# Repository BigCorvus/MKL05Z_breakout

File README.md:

# MKL05Z_breakout
Breakout board for the MKL05Z32VFM4 Corte M0 microcontroller by Freescale. 
See http://www.thinkering.de/cms/?p=656 for more info.

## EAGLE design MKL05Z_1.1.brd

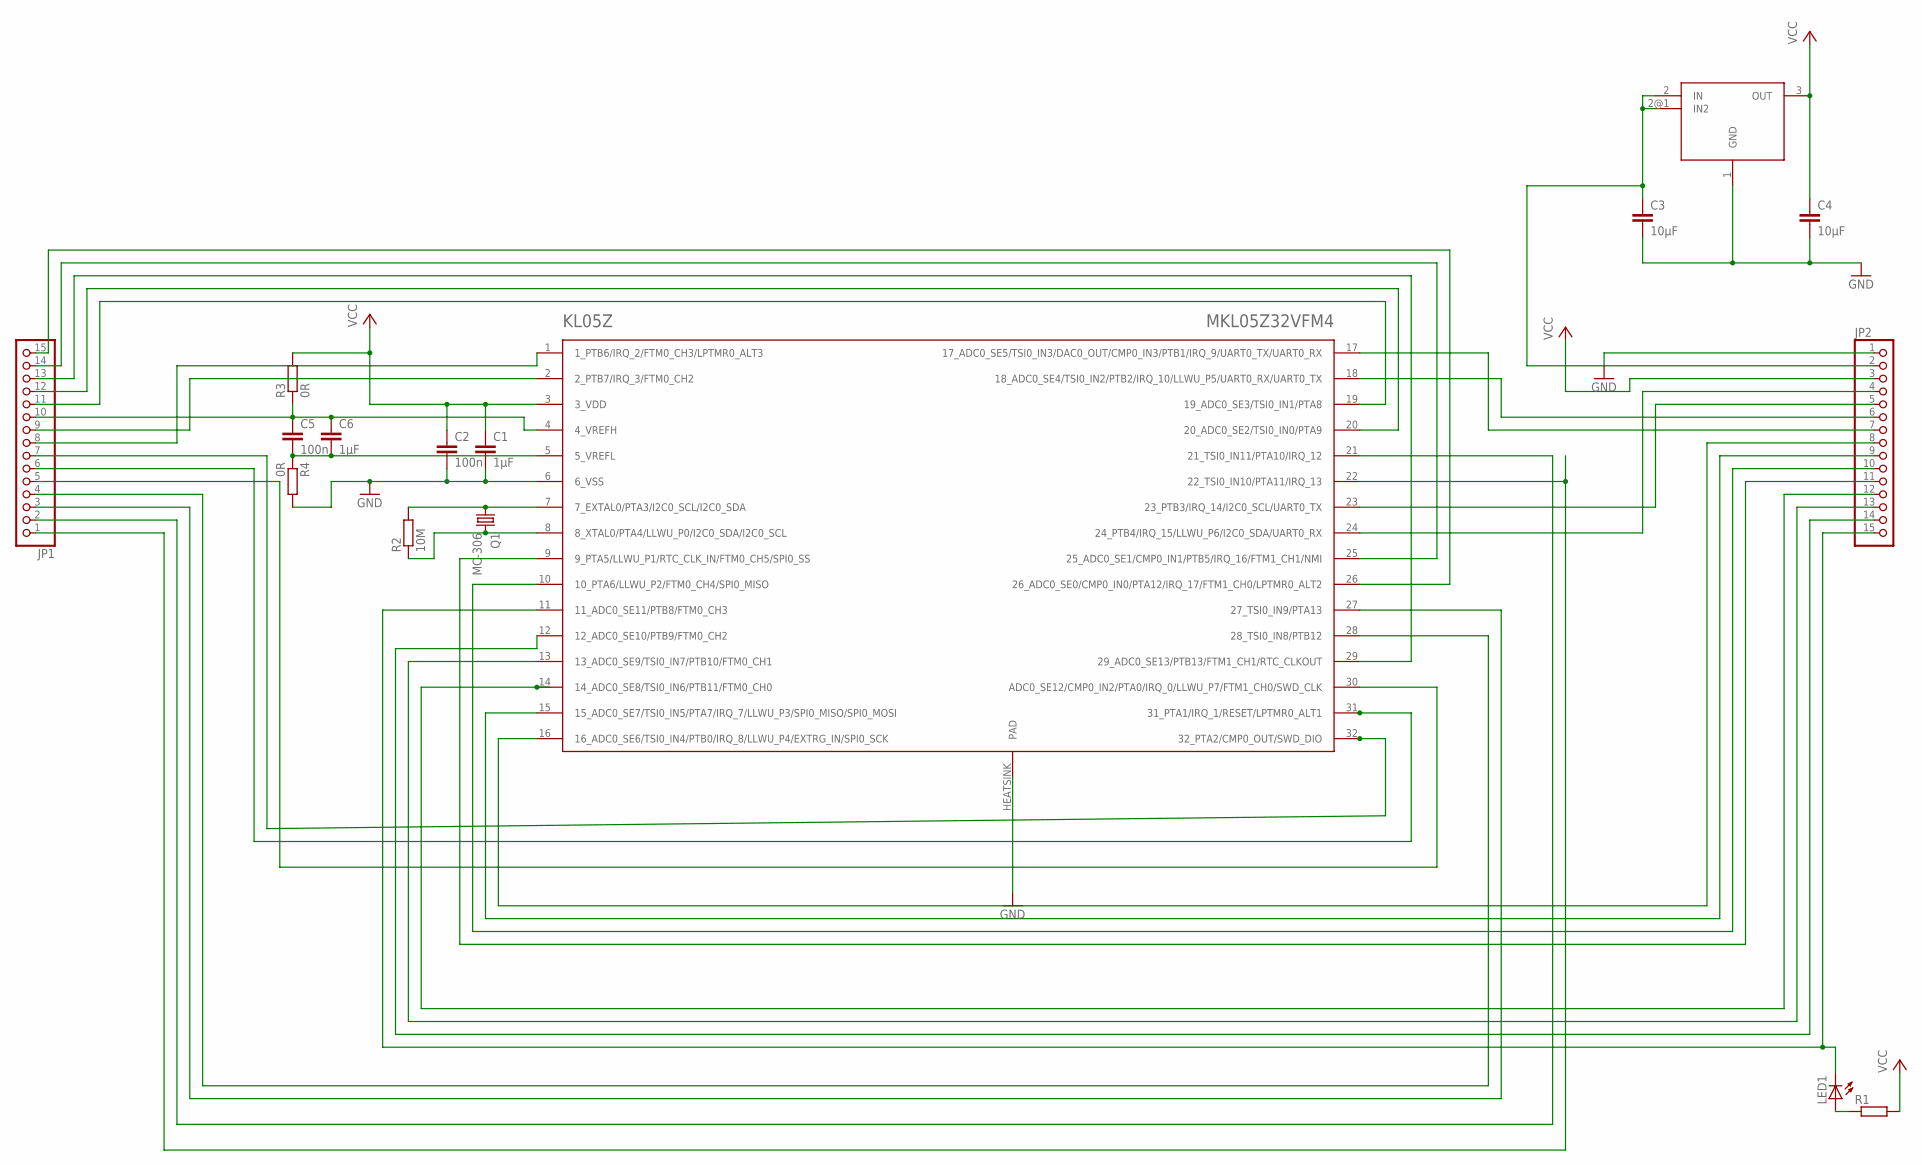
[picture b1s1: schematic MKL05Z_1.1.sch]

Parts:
C1, C6: 1µF; C0603
C2, C5: 100n; C0603
C3, C4: 10µF; C0805
JP1, JP2: PINHD-1X15; 1X15
KL05Z: MKL05Z32VFM4; QFN32
LED1: LEDCHIPLED_0805; CHIPLED_0805
Q1: MC-306
R1: R-EU_R0603; R0603
R2: 10M; R0603
R3, R4: 0R; R0402
U$1: HT7333; SOT89

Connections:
GND: C1.2, C2.2, C3.2, C4.2, JP2.1, KL05Z.6 (6_VSS), KL05Z.HEATSINK (PAD), R4.2, U$1.1 (GND)
unnamed: JP1.6, KL05Z.31 (31_PTA1/IRQ_1/RESET/LPTMR0_ALT1)
unnamed: JP1.4, KL05Z.28 (28_TSI0_IN8/PTB12)
unnamed: JP1.5, KL05Z.30 (ADC0_SE12/CMP0_IN2/PTA0/IRQ_0/LLWU_P7/F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)
unnamed: KL05Z.7 (7_EXTAL0/PTA3/I2C0_SCL/I2C0_SDA), Q1.1, R2.2
unnamed: C5.2, C6.2, KL05Z.5 (5_VREFL), R4.1
unnamed: C3.1, JP2.2, U$1.2 (IN), U$1.2@1 (IN2)
unnamed: JP2.6, KL05Z.18 (18_ADC0_SE4/TSI0_IN2/PTB2/IRQ_10/LLWU_P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)
unnamed: JP2.7, KL05Z.17 (17_ADC0_SE5/TSI0_IN3/DAC0_OUT/CMP0_IN3/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)
unnamed: JP2.4, KL05Z.24 (24_PTB4/IRQ_15/LLWU_P6/I2C0_SDA/UART0_RX)
unnamed: JP2.5, KL05Z.23 (23_PTB3/IRQ_14/I2C0_SCL/UART0_TX)
unnamed: KL05Z.8 (8_XTAL0/PTA4/LLWU_P0/I2C0_SDA/I2C0_SCL), Q1.4 (2), R2.1
unnamed: JP2.11, KL05Z.9 (9_PTA5/LLWU_P1/RTC_CLK_IN/FTM0_CH5/SPI0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)
unnamed: JP2.10, KL05Z.10 (10_PTA6/LLWU_P2/FTM0_CH4/SPI0_MISO)
unnamed: JP2.9, KL05Z.15 (15_ADC0_SE7/TSI0_IN5/PTA7/IRQ_7/LLWU_P3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)
unnamed: JP2.8, KL05Z.16 (16_ADC0_SE6/TSI0_IN4/PTB0/IRQ_8/LLWU_P4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)
unnamed: JP1.7, KL05Z.32 (32_PTA2/CMP0_OUT/SWD_DIO)
unnamed: JP1.3, KL05Z.27 (27_TSI0_IN9/PTA13)
unnamed: JP1.2, KL05Z.21 (21_TSI0_IN11/PTA10/IRQ_12)
unnamed: JP1.1, KL05Z.22 (22_TSI0_IN10/PTA11/IRQ_13)
unnamed: C5.1, C6.1, JP1.10, KL05Z.4 (4_VREFH), R3.1
unnamed: JP1.11, KL05Z.19 (19_ADC0_SE3/TSI0_IN1/PTA8)
unnamed: JP1.12, KL05Z.20 (20_ADC0_SE2/TSI0_IN0/PTA9)
unnamed: JP1.13, KL05Z.29 (29_ADC0_SE13/PTB13/FTM1_CH1/RTC_CLKOUT)
unnamed: JP1.15, KL05Z.26 (26_ADC0_SE0/CMP0_IN0/PTA12/IRQ_17/FTM1_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)
unnamed: JP1.14, KL05Z.25 (25_ADC0_SE1/CMP0_IN1/PTB5/IRQ_16/FTM1_C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)
unnamed: LED1.A, R1.1
unnamed: JP1.9, KL05Z.2 (2_PTB7/IRQ_3/FTM0_CH2)
unnamed: JP2.12, KL05Z.14 (14_ADC0_SE8/TSI0_IN6/PTB11/FTM0_CH0)
unnamed: JP1.8, KL05Z.1 (1_PTB6/IRQ_2/FTM0_CH3/LPTMR0_ALT3)
unnamed: JP2.13, KL05Z.13 (13_ADC0_SE9/TSI0_IN7/PTB10/FTM0_CH1)
unnamed: JP2.14, KL05Z.12 (12_ADC0_SE10/PTB9/FTM0_CH2)
unnamed: JP2.15, KL05Z.11 (11_ADC0_SE11/PTB8/FTM0_CH3), LED1.C
VCC: C1.1, C2.1, C4.1, JP2.3, KL05Z.3 (3_VDD), R1.2, R3.2, U$1.3 (OUT)

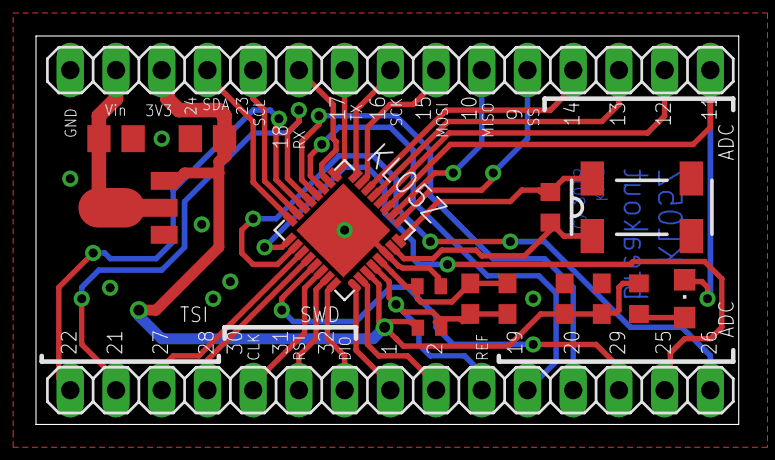
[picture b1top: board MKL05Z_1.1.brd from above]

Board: 2 copper layers, 39.0 x 21.6 mm, 16 parts (0 on the bottom side), 34 nets.

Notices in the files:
MKL05Z_1.1.brd:
(C) 2015
